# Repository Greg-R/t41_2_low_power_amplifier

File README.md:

The documentation for this module is located here:

<https://kf5n.com/t41-2/low_power_amplifier/>

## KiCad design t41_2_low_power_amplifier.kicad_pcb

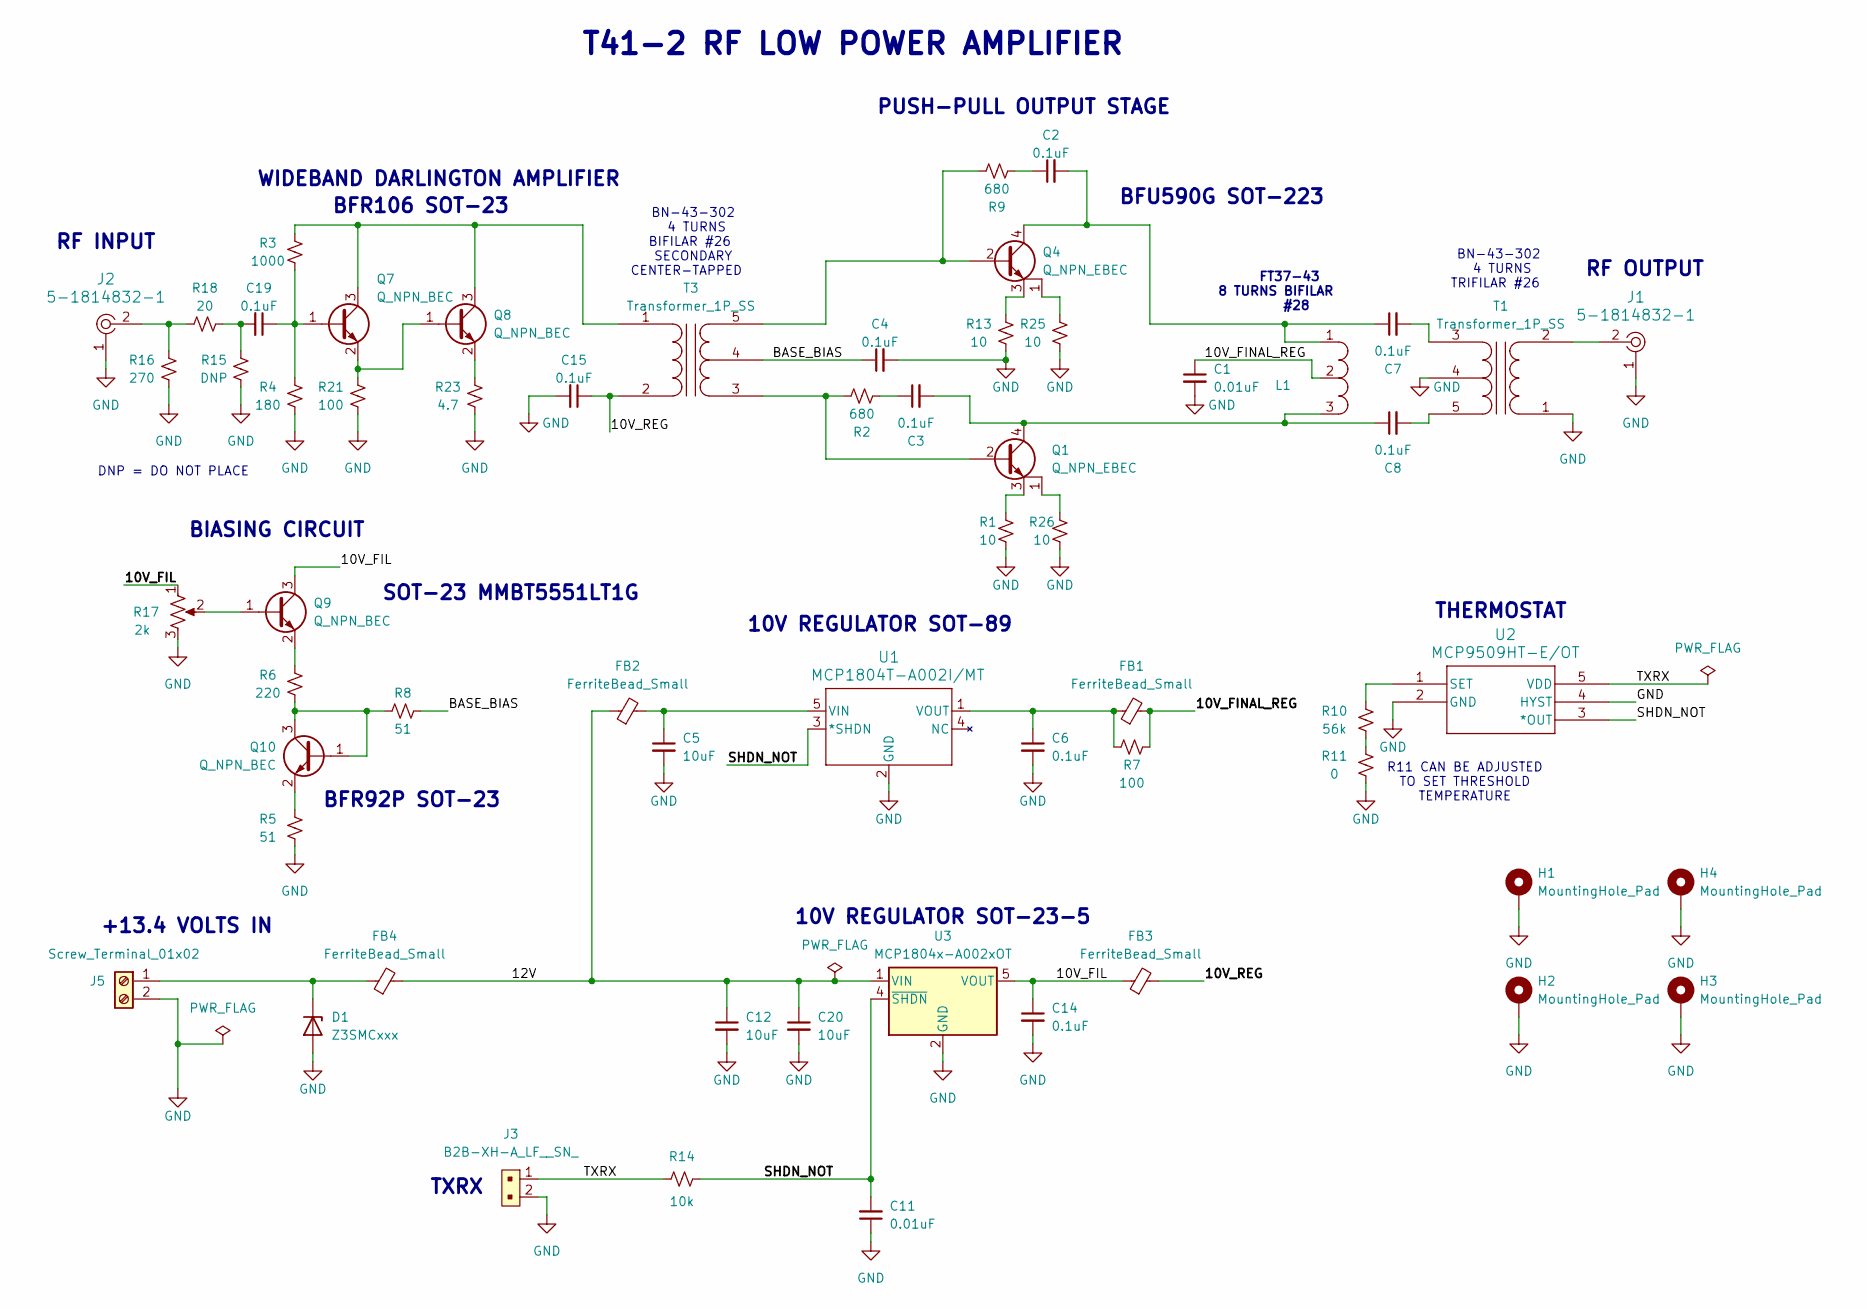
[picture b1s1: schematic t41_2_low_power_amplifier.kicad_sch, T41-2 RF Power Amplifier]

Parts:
C1, C11: 0.01uF; C_1206_3216Metric
C2, C3, C4, C6, C7, C8, C14, C15, C19: 0.1uF; C_1206_3216Metric
C5, C12, C20: 10uF; C_1206_3216Metric
D1: Z3SMCxxx; D_SMC
FB1, FB2, FB3, FB4: FerriteBead_Small; L_1206_3216Metric
H1, H2, H3, H4: MountingHole_Pad; MountingHole_4.3mm_M4_DIN965_Pad
J1, J2: 5-1814832-1; RF_SMA_Vertical_5-1814832-1; MPN 5-1814832-1; Digi-Key_PN A97594-ND
J3: B2B-XH-A_LF__SN_; PinHeader_1x2_P2.5mm_Drill1.1mm; MPN B2B-XH-A(LF)(SN); Digi-Key_PN 455-2247-ND
J5: Screw_Terminal_01x02; TerminalBlock_Philmore_TB132_1x02_P5.00mm_Horizontal
L1: FT37-43
Q1, Q4: Q_NPN_EBEC; SOT-223
Q7, Q8, Q9, Q10: Q_NPN_BEC; SOT-23-3
R1, R13, R25, R26: 10; R_1206_3216Metric
R2, R9: 680; R_1206_3216Metric
R3: 1000; R_1206_3216Metric
R4: 180; R_1206_3216Metric
R5, R8: 51; R_1206_3216Metric
R6: 220; R_1206_3216Metric
R7, R21: 100; R_1206_3216Metric
R10: 56k; R_1206_3216Metric
R11: 0; R_1206_3216Metric
R14: 10k; R_1206_3216Metric
R15: DNP; R_1206_3216Metric
R16: 270; R_1206_3216Metric
R17: 2k; Potentiometer_Bourns_3296W_Vertical
R18: 20; R_1206_3216Metric
R23: 4.7; R_1206_3216Metric
T1, T3: Transformer_1P_SS; BN-43-302_Vertical
U1: MCP1804T-A002I/MT; SOT-89_5MC_MCH
U2: MCP9509HT-E/OT; SOT-23-5_MC_MCH
U3: MCP1804x-A002xOT; SOT-23-5

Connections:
/10V_FIL: C14.1, FB3.1, Q9.3 (C), R17.1, U3.5 (VOUT)
/10V_FINAL_REG: C1.1, FB1.2, L1.2, R7.1
/10V_REG: C15.1, FB3.2, T3.2 (AB)
/12V: C12.1, C20.1, FB2.1, FB4.2, U3.1 (VIN)
/BASE_BIAS: C4.1, R8.1, T3.4 (SC)
/SHDN_NOT: C11.2, R14.2, U1.3 (*SHDN), U2.3 (*OUT), U3.4 (~SHDN)
/TXRX: J3.1, R14.1, U2.5 (VDD)
GND: C1.2, C4.2, C5.2, C6.2, C11.1, C12.2, C14.2, C15.2, C20.2, D1.2 (A), H1.1, H2.1, H3.1, H4.1, J1.1, J2.1, J3.2, J5.2, R1.1, R4.1, R5.1, R11.2, R13.1, R15.1, R16.1, R17.3, R21.1, R23.1, R25.1, R26.1, T1.1 (AA), T1.4 (SC), U1.2 (GND), U2.2 (GND), U2.4 (HYST), U3.2 (GND)
unnamed: C2.1, R9.1
unnamed: C3.1, R2.1
unnamed: C19.2, R15.2, R18.2
unnamed: D1.1 (K), FB4.1, J5.1
unnamed: J2.2, R16.2, R18.1
unnamed: Q1.2 (B), R2.2, T3.3 (SA)
unnamed: C3.2, C8.1, L1.3, Q1.4 (C)
unnamed: Q1.3 (E), R1.2
unnamed: Q1.1, R26.2
unnamed: Q4.2 (B), R9.2, T3.5 (SB)
unnamed: C2.2, C7.1, L1.1, Q4.4 (C)
unnamed: Q4.3 (E), R13.2
unnamed: Q4.1, R25.2
unnamed: C19.1, Q7.1 (B), R3.1, R4.2
unnamed: Q7.3 (C), Q8.3 (C), R3.2, T3.1 (AA)
unnamed: Q7.2 (E), Q8.1 (B), R21.2
unnamed: Q8.2 (E), R23.2
unnamed: Q9.1 (B), R17.2
unnamed: Q9.2 (E), R6.2
unnamed: Q10.1 (B), Q10.3 (C), R6.1, R8.2
unnamed: Q10.2 (E), R5.2
unnamed: R10.2, R11.1
unnamed: J1.2, T1.2 (AB)
unnamed: C7.2, T1.3 (SA)
unnamed: C8.2, T1.5 (SB)
unnamed: C5.1, FB2.2, U1.5 (VIN)
unnamed: C6.1, FB1.1, R7.2, U1.1 (VOUT)
unnamed: R10.1, U2.1 (SET)

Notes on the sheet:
RF OUTPUT
THERMOSTAT
PUSH-PULL OUTPUT STAGE
BN-43-302 4 TURNS TRIFILAR #26
R11 CAN BE ADJUSTED TO SET THRESHOLD TEMPERATURE
BFU590G SOT-223
BIASING CIRCUIT
SOT-23 MMBT5551LT1G
+13.4 VOLTS IN
TXRX
FT37-43 8 TURNS BIFILAR #28
DNP = DO NOT PLACE
T41-2 RF LOW POWER AMPLIFIER
BFR106 SOT-23
RF INPUT
10V REGULATOR SOT-23-5
BN-43-302 4 TURNS BIFILAR #26 SECONDARY CENTER-TAPPED
WIDEBAND DARLINGTON AMPLIFIER
BFR92P SOT-23
10V REGULATOR SOT-89

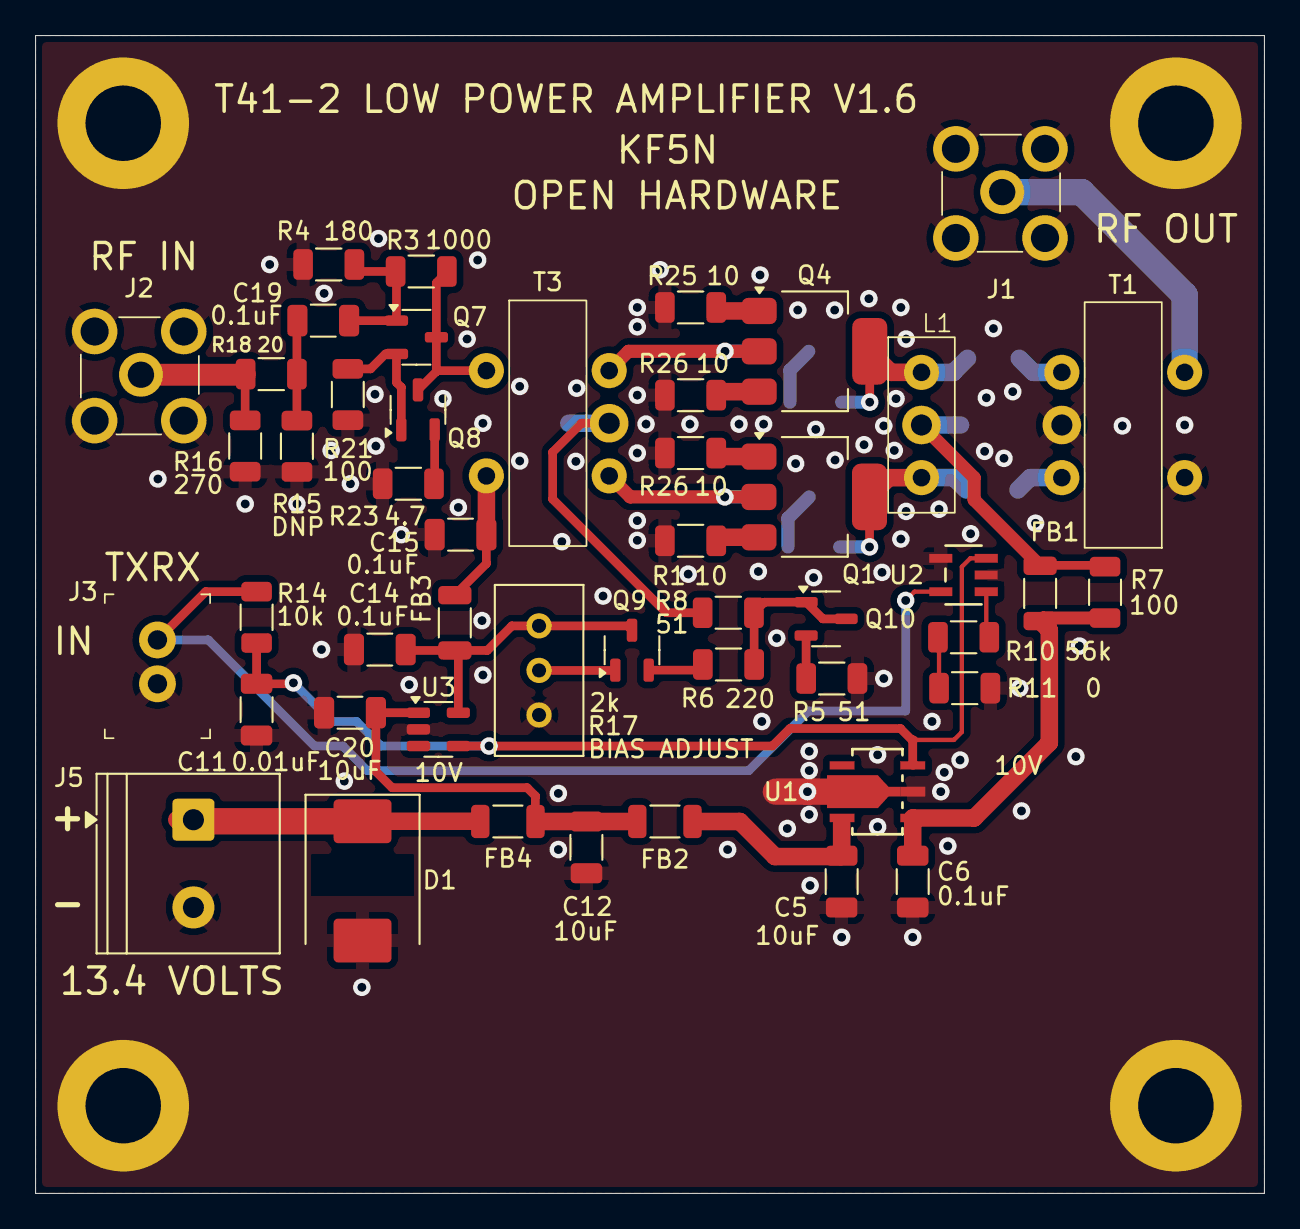
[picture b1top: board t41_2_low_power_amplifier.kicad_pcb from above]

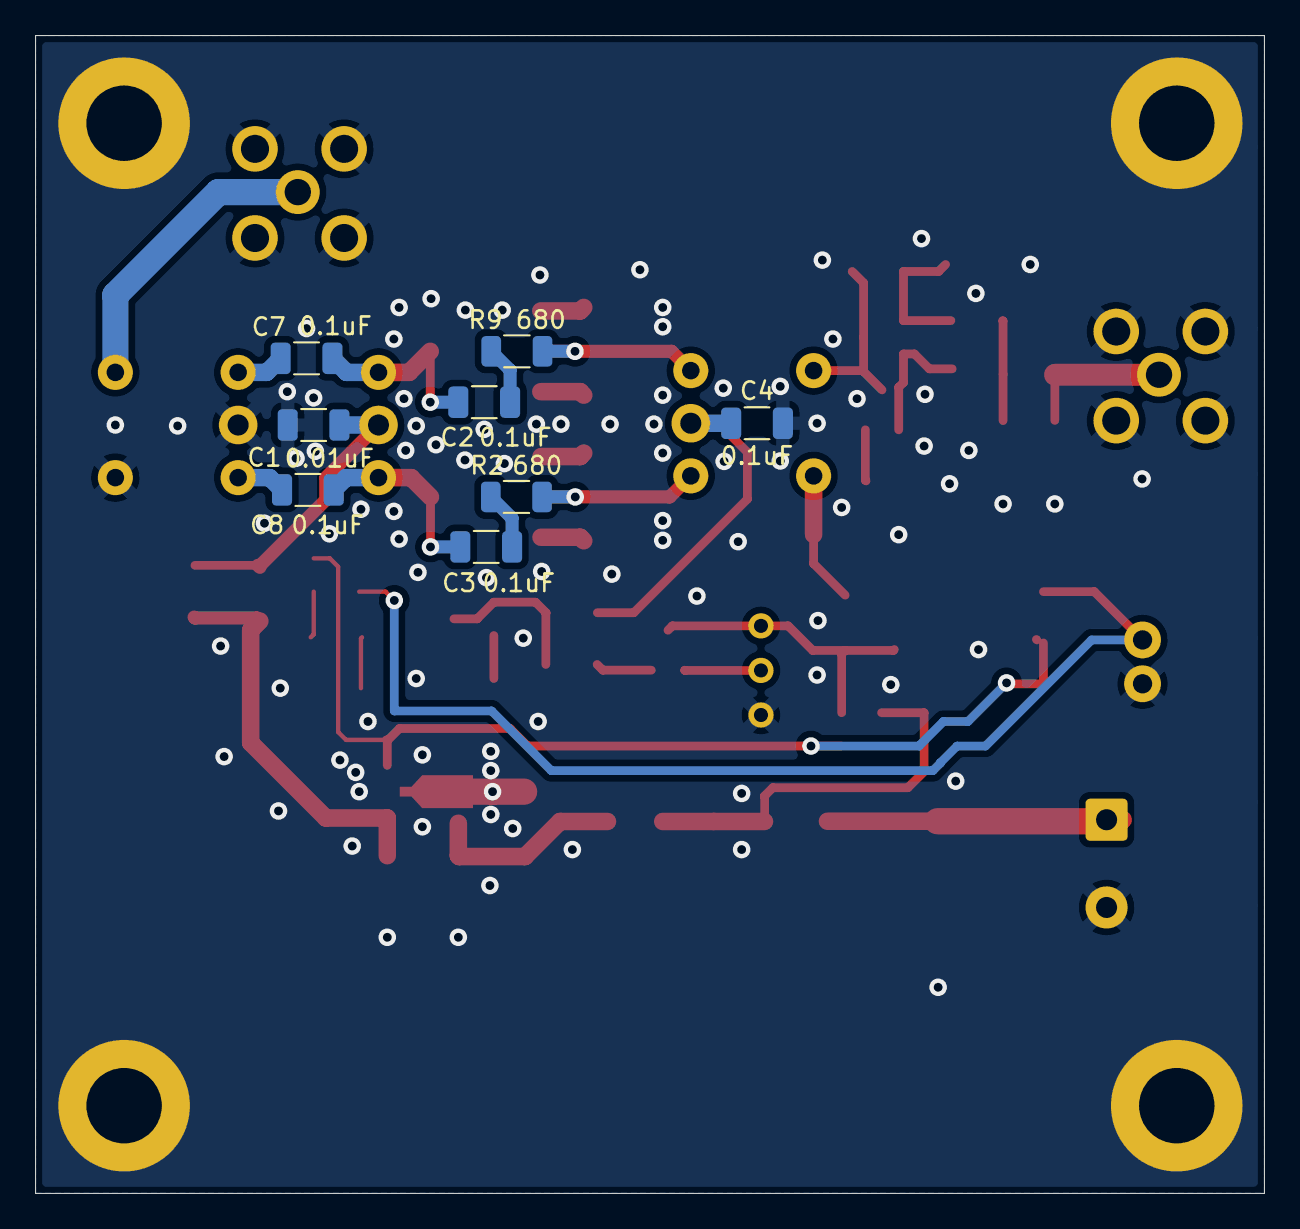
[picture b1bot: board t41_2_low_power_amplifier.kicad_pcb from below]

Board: 2 copper layers, 70.1 x 66.0 mm, 60 parts (8 on the bottom side), 36 nets.

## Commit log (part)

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2024-11-08 Initial commit.
2024-11-11 First version complete and sent to fab.
2024-11-30 Most routing completed.
2024-12-01 Low Power Amplifier ready for fab.
2024-12-22 T41-2 Low Power Amplifier to fab.
2025-01-19 Low Power Amplifier to fab.
2025-04-23 Release to fab.
2025-05-05 Updated notes on schematic.
2025-05-05 Updated schematic notes.
2025-06-16 Finishing up version 1.5. Not ready for fab.
2025-06-22 Work in progress.
2025-06-23 Added Chernobyl device.
2025-06-23 Ready for fab.
2025-07-05 Clean up for publish.
2025-07-05 Cleaning up initial push to Github.
2025-07-06 Added preliminary README file.
2025-07-07 Working on README.
2025-07-07 Updated README.
2025-07-07 Fixed link to Kits and Parts.
2025-07-07 Added licensing.
2025-07-07 Added comment to README.
2026-05-23 Minor schematic update.
